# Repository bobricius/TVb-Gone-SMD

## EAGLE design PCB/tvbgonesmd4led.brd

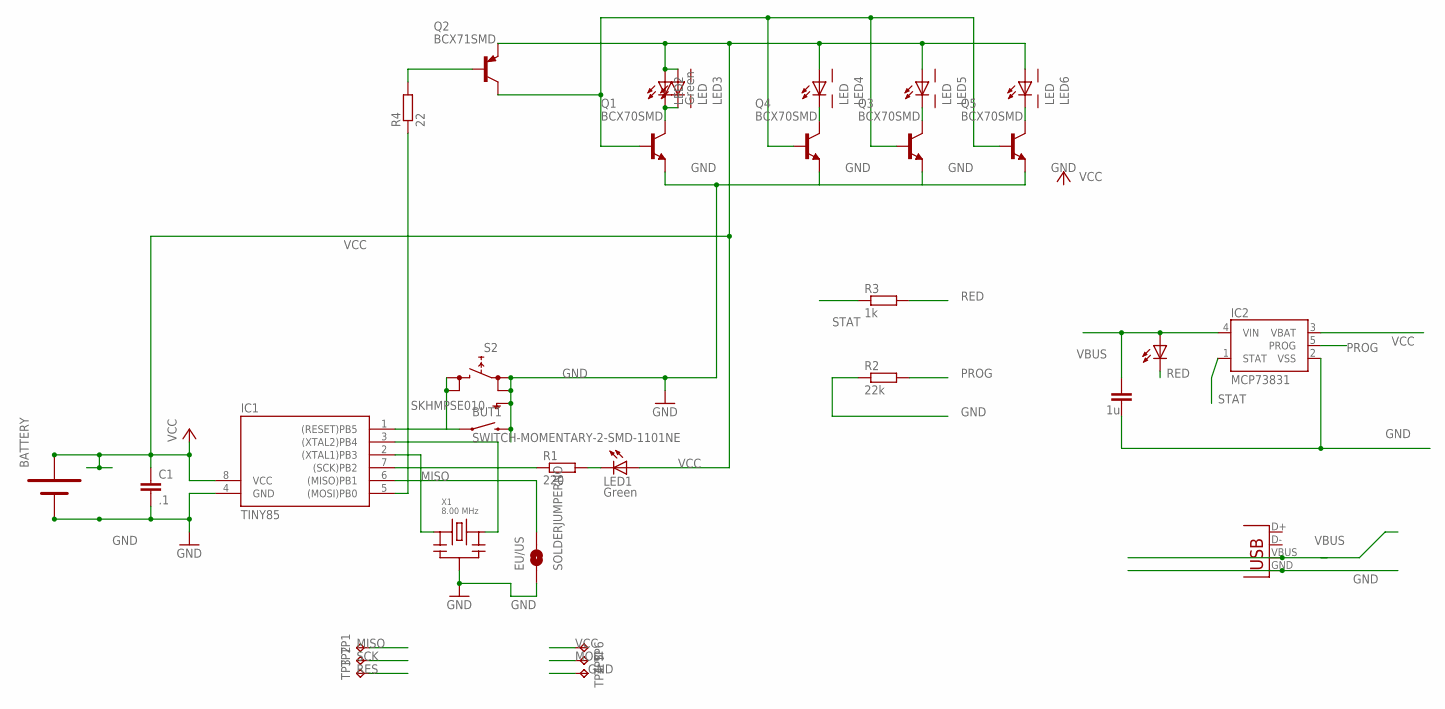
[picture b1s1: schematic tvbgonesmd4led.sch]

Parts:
BATTERY: BATTERY-1XAA20MM; BATTCOM_20MM_PTH
BUT1: SWITCH-MOMENTARY-2-SMD-1101NE; TACTILE-SWITCH-1101NE
C1: .1; C0603
C2: 1u; C0603
CHG: 0805; CHIPLED_0603
EU/US: SOLDERJUMPERNO; SJ_2S-NO
IC1: TINY85; SOIC8
IC2: MCP73831; SOT23-5
LED1: Green; CHIPLED_0603
LED2: Green; CHIPLED_0805
LED3, LED4, LED5, LED6: LED; 5MM-SIDE
Q1, Q3, Q4, Q5: BCX70SMD; SOT23
Q2: BCX71SMD; SOT23
R1: 220; R0603
R2: 22k; R0603
R3: 1k; R0603
R4: 22; R0603
S2: SKHMPSE010; SKHMPXE010
TP1, TP2, TP3, TP4, TP5, TP6: TPB1,27; B1,27
X1: 8.00 MHz; AWSCR
X6: USB-MICROB

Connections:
GND: BATTERY.-, BUT1.P$2 (2), C1.2, C2.2, EU/US.1, IC1.4 (GND), IC2.2 (VSS), Q1.2 (E), Q3.2 (E), Q4.2 (E), Q5.2 (E), R2.1, S2.1 (1.1), S2.2 (1.2), S2.5 (SH), TP4.TP, X1.P$2 (GND), X6.GND
MISO: EU/US.2, IC1.6 ((MISO)PB1), TP1.TP
MOSI: IC1.5 ((MOSI)PB0), R4.1, TP5.TP
unnamed: LED2.C, LED3.K (C), Q1.3 (C)
unnamed: IC1.2 ((XTAL1)PB3), X1.P$1
unnamed: LED1.C, R1.2
unnamed: IC1.3 ((XTAL2)PB4), X1.P$3
unnamed: Q2.1 (B), R4.2
unnamed: Q1.1 (B), Q2.3 (C), Q3.1 (B), Q4.1 (B), Q5.1 (B)
unnamed: LED4.K (C), Q4.3 (C)
unnamed: LED5.K (C), Q3.3 (C)
unnamed: LED6.K (C), Q5.3 (C)
PROG: IC2.5 (PROG), R2.2
RED: CHG.C, R3.2
RES: BUT1.P$1 (1), IC1.1 ((RESET)PB5), S2.3 (2.1), S2.4 (2.2), TP3.TP
SCK: IC1.7 ((SCK)PB2), R1.1, TP2.TP
STAT: IC2.1 (STAT), R3.1
VBUS: C2.1, CHG.A, IC2.4 (VIN), X6.VBUS
VCC: BATTERY.+, C1.1, IC1.8 (VCC), IC2.3 (VBAT), LED1.A, LED2.A, LED3.A, LED4.A, LED5.A, LED6.A, Q2.2 (E), TP6.TP

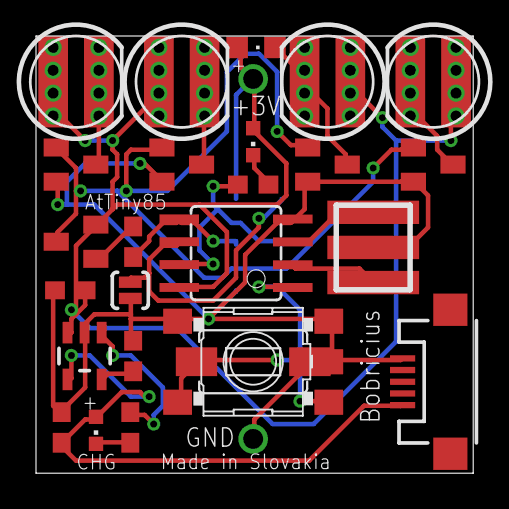
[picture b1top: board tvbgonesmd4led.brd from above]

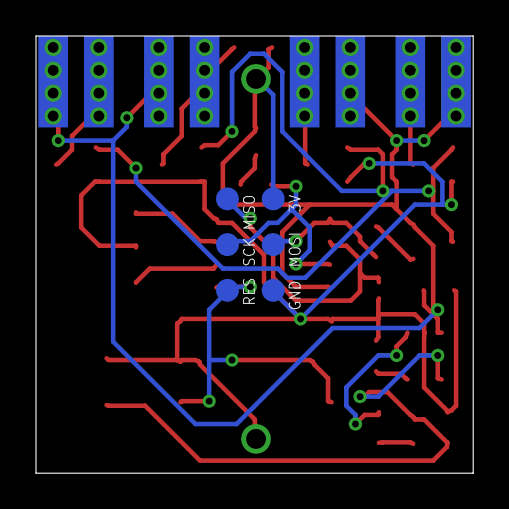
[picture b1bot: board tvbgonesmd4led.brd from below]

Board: 2 copper layers, 24.3 x 24.3 mm, 32 parts (6 on the bottom side), 19 nets.

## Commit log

2014-11-12 :space_invader: Added .gitattributes
2014-11-12 First upload
    nothing new

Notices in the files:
parts and their libraries:
SparkFun: Licensing: CC v3.0 Share-Alike You are welcome to use this library for commercial purposes.
